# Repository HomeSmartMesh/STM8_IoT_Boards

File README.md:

# See these boards in action in the repo [IoT_Frameworks](https://github.com/wassfila/IoT_Frameworks)

# STM8_IoT_Boards
This repository provides PCBs based on the STM8 which is the cheapest microcontroller on the market (Low and production volumes) with the cheapest debug and development environment.

## IoT Node (RF but Connected to Power)
PCB design using the STM8S103F bread board with the nRF24L01+ module. Provides connectors for I²C, UART and One wire.
 - [STM8S fixed Node wiki page](http://technolab.ddns.net/display/SSN/STM8S+Fixed+Node)

## Smart IoT Node (Wireless and Cell Coin Powered)
This Board includes an STM8L151F3P6 (Low Power) the nRF24L01+, sensors modules : BMP280 (pressure, humidity, temperature), a MAX44009 (Ambient Light) and MRMS211H (Magnetic switches).
 - [STM8L Mobile Node wiki page](http://technolab.ddns.net/display/SSN/STM8L+Mobile+Node)

## IO_Expander
serial port commands issued in an ULN2804 general purpose up to 48V or 500mA per output
 - [Github Repository for nodejs websocket server with javascript gui](https://github.com/wassfila/smartio)
 - [IO Expander wiki page](http://technolab.ddns.net/display/SSN/Smart+IO+Expander)

## Servomotor Controller
This board uses the 16 bit x7 channels PWM (from different timers) used to generate pulses for servomotors.
 - [Available PS4 wireless on Raspberry Pi 3 application source codes](https://github.com/wassfila/joystick_servo)

# Links to Firmware Sources
 - [Hello World Examples](https://github.com/wassfila/STM8_IoT_HelloWorld)
 - [Complete Usecase Examples e.g. Sender + Receiver](https://github.com/wassfila/STM8_IoT_Base)

# More Info
The IoT node is an STM8 based low cost development platform.
It is an initiative for an open product = open hardware + open source project.
find all the details in this link :
http://www.homesmartmesh.com/mediawiki/index.php/IoT_Node

This board will be interfacing such peripherals :
 - Radio transceiver module
 - Weather sensors : temperature, humidity, air quality.
 - RGB Leds
 - Gyro / Accel
 - Ambient light and user gesture

The wiki above contains links to SW and HW, but here's a direct link to the Firmware open source project:
https://github.com/wassfila/STM8_IoT_HelloWorld
The Firmware contains drivers (in development) for the above mentionned peripherals.

This IoT Node is part of a bigger project that extand the collaboration to a complete IoT environment.
It includes  interfaces to existing products and server applications for merging everything together.
The "Home Smart Mesh" concept is described in the main wiki page
http://www.homesmartmesh.com/mediawiki/index.php/Main_Page

The Board is grouping two modules :
 - STM8 Dev Board based on the STM8S103F3
 - nRF24L01+ module based on the reference design
 - It also has a pullup resistor and 3 pins where to plug an DS18B20 temperature sensor

# License
- It is possible to use these designs for commercial purpose
- It is possible to modify the designs
- It is not necessary to mention the original author of these designs
- It is possible to add your own name or company on the design
- It is not possible to prevent anyone else from having the rights mentionned above

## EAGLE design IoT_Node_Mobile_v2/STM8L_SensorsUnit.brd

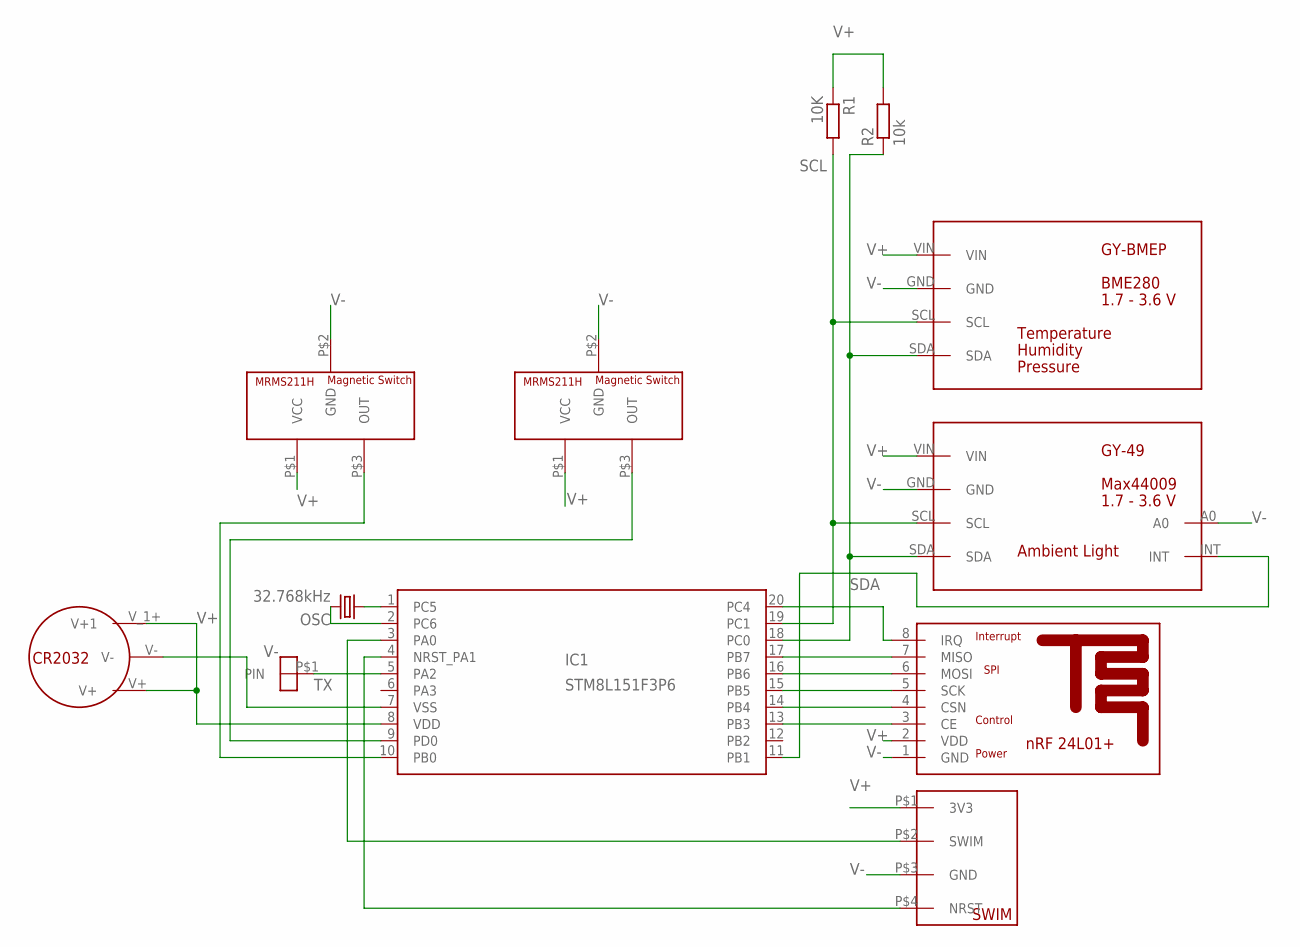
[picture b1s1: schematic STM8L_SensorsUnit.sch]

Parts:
IC1: STM8L151F3P6; STM8L151F3P
OSC: 32.768kHz; CRYSTAL-SMD-3.2X1.5MM
R1: 10K; M1206
R2: 10k; M1206
U$1: NRF24L01+REFDESIGNMINI; NRF24L01+REFDESIGN-MINI
U$2: GY-49G-49-SURF; GY-49-SURF
U$3: GY-BMEPGY-BMEP-NOHOLE; GY-BMEP-NOHOLE
U$4, U$6: MRMS211H-MAGNETIC-SWITCH; 3PIN-MM
U$5: CR2032-ISOLATED
U$7: SWIM
U$8: PINSIGNAL; PIN

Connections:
unnamed: IC1.16 (PB6), U$1.6 (MOSI)
unnamed: IC1.14 (PB4), U$1.4 (CSN)
unnamed: IC1.13 (PB3), U$1.3 (CE)
unnamed: IC1.10 (PB0), U$6.P$3 (OUT)
unnamed: IC1.9 (PD0), U$4.P$3 (OUT)
unnamed: IC1.20 (PC4), U$1.8 (IRQ)
unnamed: IC1.3 (PA0), U$7.P$2 (SWIM)
unnamed: IC1.4 (NRST_PA1), U$7.P$4 (NRST)
unnamed: IC1.1 (PC5), OSC.P$1 (1)
unnamed: IC1.11 (PB1), U$2.INT
unnamed: IC1.2 (PC6), OSC.P$2 (2)
unnamed: IC1.17 (PB7), U$1.7 (MISO)
unnamed: IC1.15 (PB5), U$1.5 (SCK)
SCL: IC1.19 (PC1), R1.2, U$2.SCL, U$3.SCL
SDA: IC1.18 (PC0), R2.1, U$2.SDA, U$3.SDA
TX: IC1.5 (PA2), U$8.P$1
V+: IC1.8 (VDD), R1.1, R2.2, U$1.2 (VDD), U$2.VIN, U$3.VIN, U$4.P$1 (VCC), U$5.V+, U$5.V_1+ (V+1), U$6.P$1 (VCC), U$7.P$1 (3V3)
V-: IC1.7 (VSS), U$1.1 (GND), U$2.A0, U$2.GND, U$3.GND, U$4.P$2 (GND), U$5.V-, U$6.P$2 (GND), U$7.P$3 (GND)

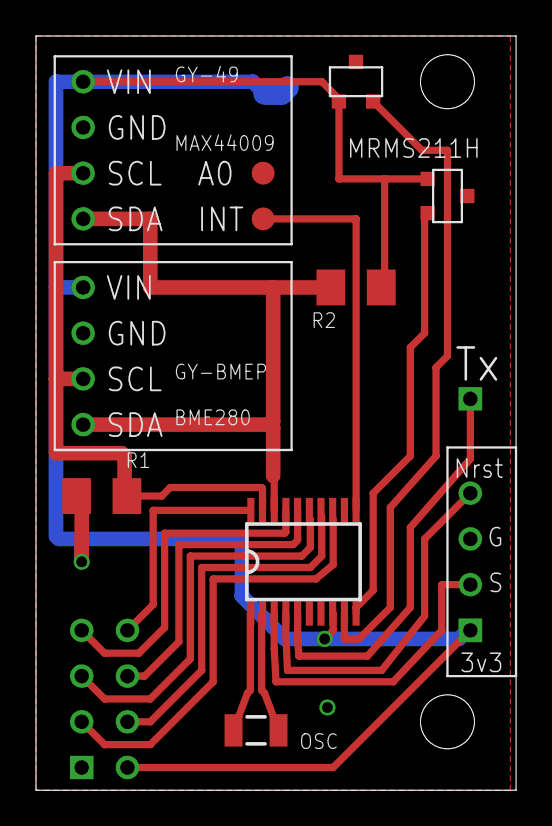
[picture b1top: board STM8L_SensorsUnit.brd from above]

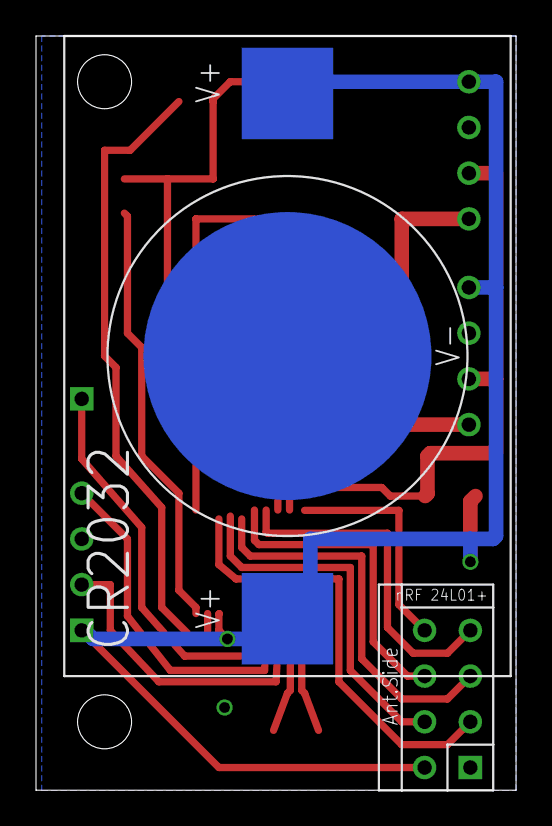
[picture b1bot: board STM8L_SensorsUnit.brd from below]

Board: 2 copper layers, 26.7 x 41.9 mm, 12 parts (2 on the bottom side), 18 nets.

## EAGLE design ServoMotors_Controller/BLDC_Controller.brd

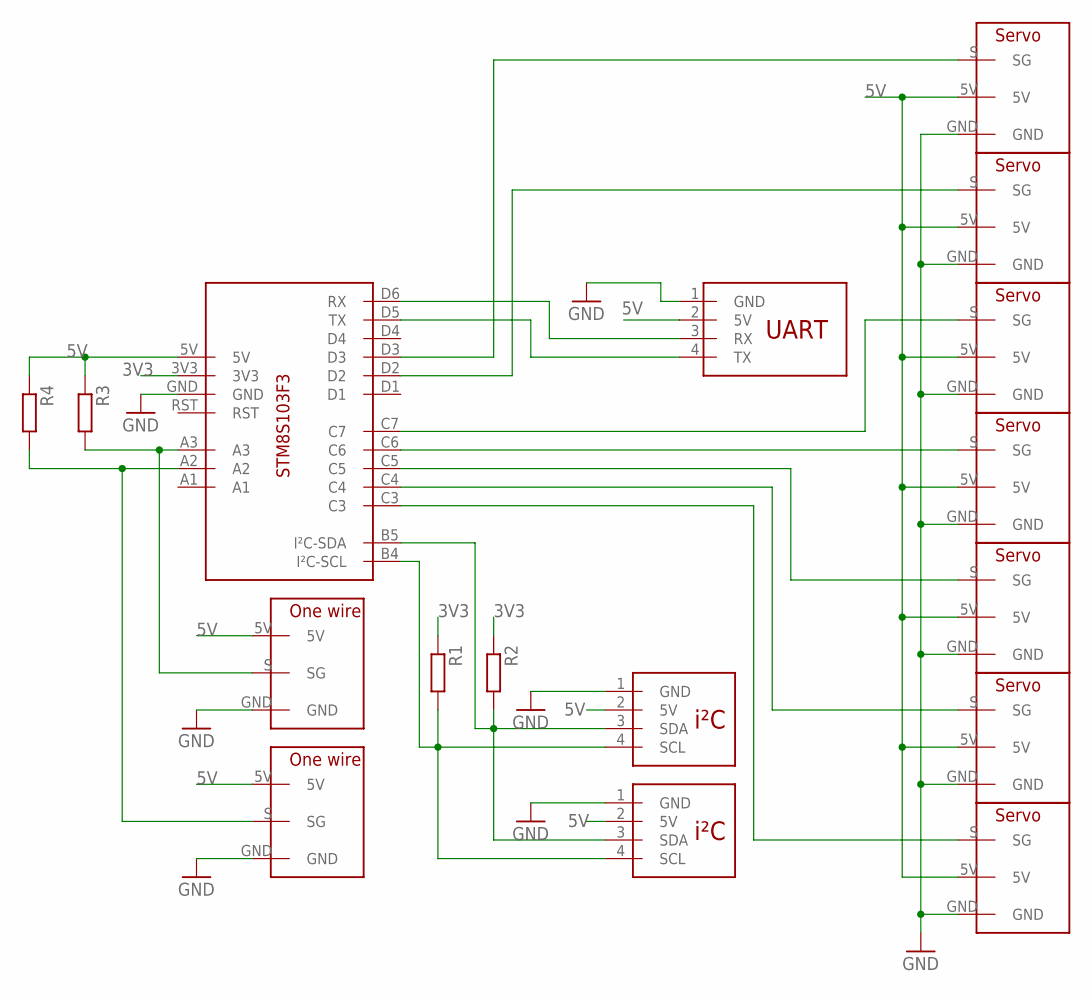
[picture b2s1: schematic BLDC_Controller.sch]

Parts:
R1, R2, R3, R4: 1k; R1206
U$1: STM8S103F3-DEVKITMINI; STM8S103F3-DEVKIT-MINI
U$2, U$8, U$9, U$10, U$11, U$12, U$13: SERVO
U$3: UARTMINI; UART-MINI
U$4, U$7: I2CMINI; I2C-MINI
U$5, U$6: ONE_WIRE

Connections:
3V3: R1.1, R2.1, U$1.3V3
5V: R3.1, R4.1, U$1.5V, U$2.5V, U$3.2 (5V), U$4.2 (5V), U$5.5V, U$6.5V, U$7.2 (5V), U$8.5V, U$9.5V, U$10.5V, U$11.5V, U$12.5V, U$13.5V
GND: U$1.GND, U$2.GND, U$3.1 (GND), U$4.1 (GND), U$5.GND, U$6.GND, U$7.1 (GND), U$8.GND, U$9.GND, U$10.GND, U$11.GND, U$12.GND, U$13.GND
unnamed: U$1.D5 (TX), U$3.4 (TX)
unnamed: U$1.C3, U$13.S (SG)
unnamed: U$1.C4, U$12.S (SG)
unnamed: U$1.C5, U$10.S (SG)
unnamed: U$1.C6, U$9.S (SG)
unnamed: U$1.C7, U$8.S (SG)
unnamed: R2.2, U$1.B5 (I²C-SDA), U$4.3 (SDA), U$7.3 (SDA)
unnamed: U$1.D2, U$2.S (SG)
unnamed: U$1.D6 (RX), U$3.3 (RX)
unnamed: R3.2, U$1.A3, U$6.S (SG)
unnamed: U$1.D3, U$11.S (SG)
unnamed: R4.2, U$1.A2, U$5.S (SG)
unnamed: R1.2, U$1.B4 (I²C-SCL), U$4.4 (SCL), U$7.4 (SCL)

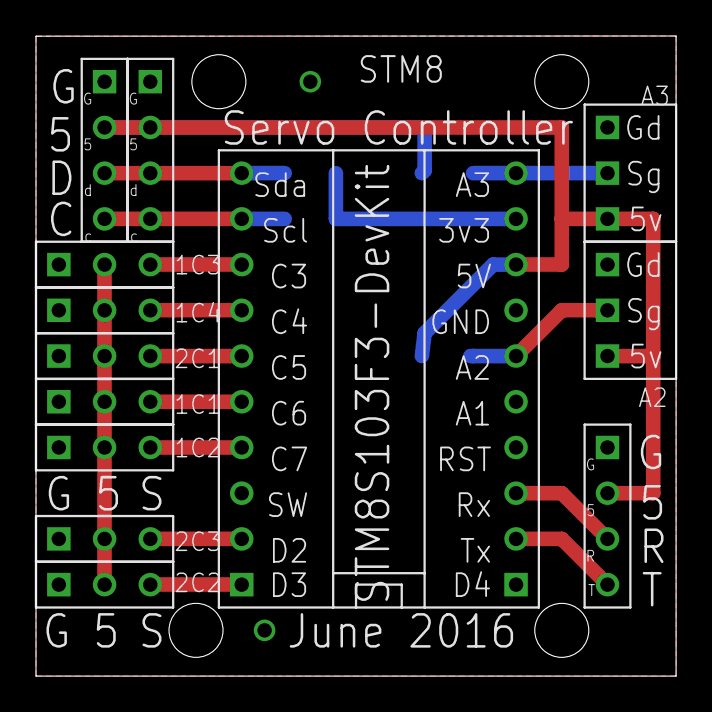
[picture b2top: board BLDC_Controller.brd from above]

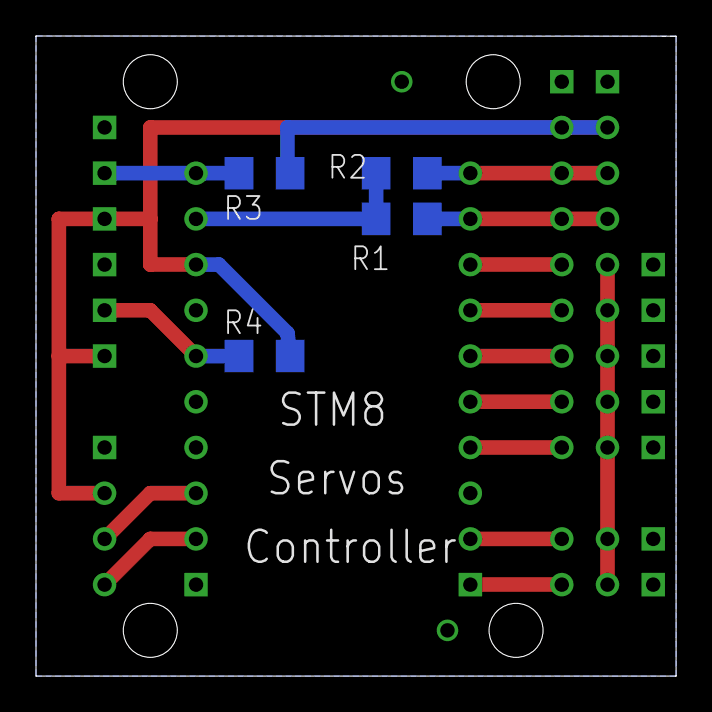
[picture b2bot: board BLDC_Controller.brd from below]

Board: 2 copper layers, 35.6 x 35.6 mm, 17 parts (4 on the bottom side), 16 nets.

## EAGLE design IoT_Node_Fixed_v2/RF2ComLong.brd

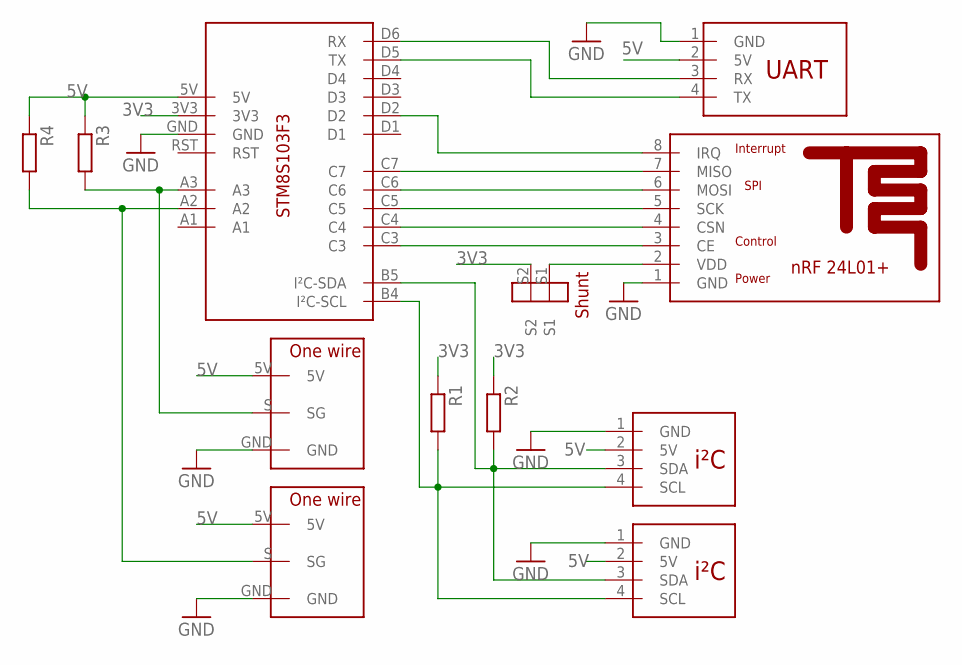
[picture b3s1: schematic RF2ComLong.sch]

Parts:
R1, R2, R3, R4: 1k; R1206
U$1: STM8S103F3-DEVKITMINI; STM8S103F3-DEVKIT-MINI
U$2: NRF24L01+REFDESIGNMINI; NRF24L01+REFDESIGN-MINI
U$3: UARTMINI; UART-MINI
U$4, U$7: I2CMINI; I2C-MINI
U$5, U$6: ONE_WIRE
U$8: SMD_SHUNT

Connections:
3V3: R1.1, R2.1, U$1.3V3, U$8.S2
5V: R3.1, R4.1, U$1.5V, U$3.2 (5V), U$4.2 (5V), U$5.5V, U$6.5V, U$7.2 (5V)
GND: U$1.GND, U$2.1 (GND), U$3.1 (GND), U$4.1 (GND), U$5.GND, U$6.GND, U$7.1 (GND)
unnamed: U$1.D5 (TX), U$3.4 (TX)
unnamed: U$1.C3, U$2.3 (CE)
unnamed: U$1.C4, U$2.4 (CSN)
unnamed: U$1.C5, U$2.5 (SCK)
unnamed: U$1.C6, U$2.6 (MOSI)
unnamed: U$1.C7, U$2.7 (MISO)
unnamed: R2.2, U$1.B5 (I²C-SDA), U$4.3 (SDA), U$7.3 (SDA)
unnamed: U$1.D2, U$2.8 (IRQ)
unnamed: U$1.D6 (RX), U$3.3 (RX)
unnamed: R3.2, U$1.A3, U$6.S (SG)
unnamed: R4.2, U$1.A2, U$5.S (SG)
unnamed: R1.2, U$1.B4 (I²C-SCL), U$4.4 (SCL), U$7.4 (SCL)
unnamed: U$2.2 (VDD), U$8.S1

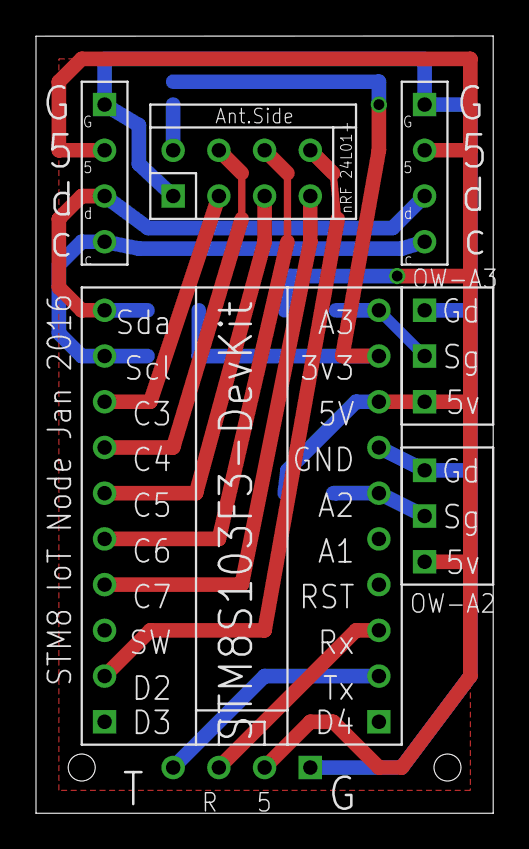
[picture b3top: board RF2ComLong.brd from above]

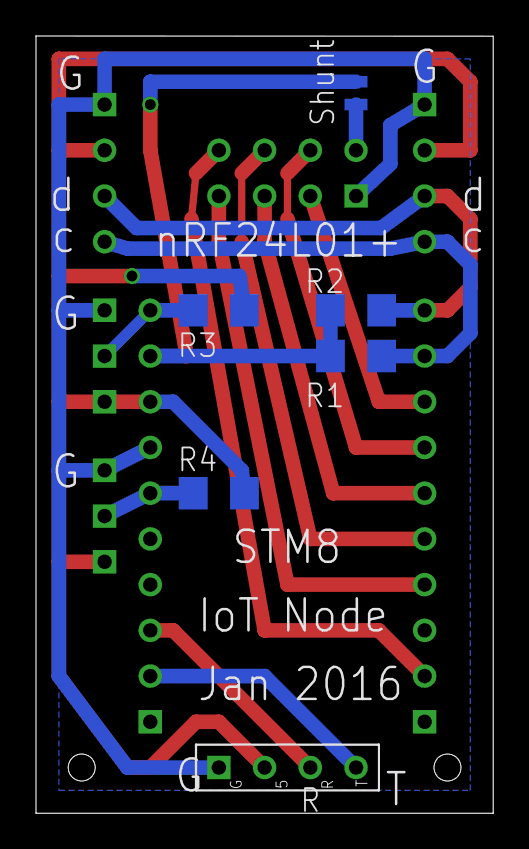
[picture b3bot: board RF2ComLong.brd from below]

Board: 2 copper layers, 25.4 x 43.2 mm, 12 parts (6 on the bottom side), 16 nets.

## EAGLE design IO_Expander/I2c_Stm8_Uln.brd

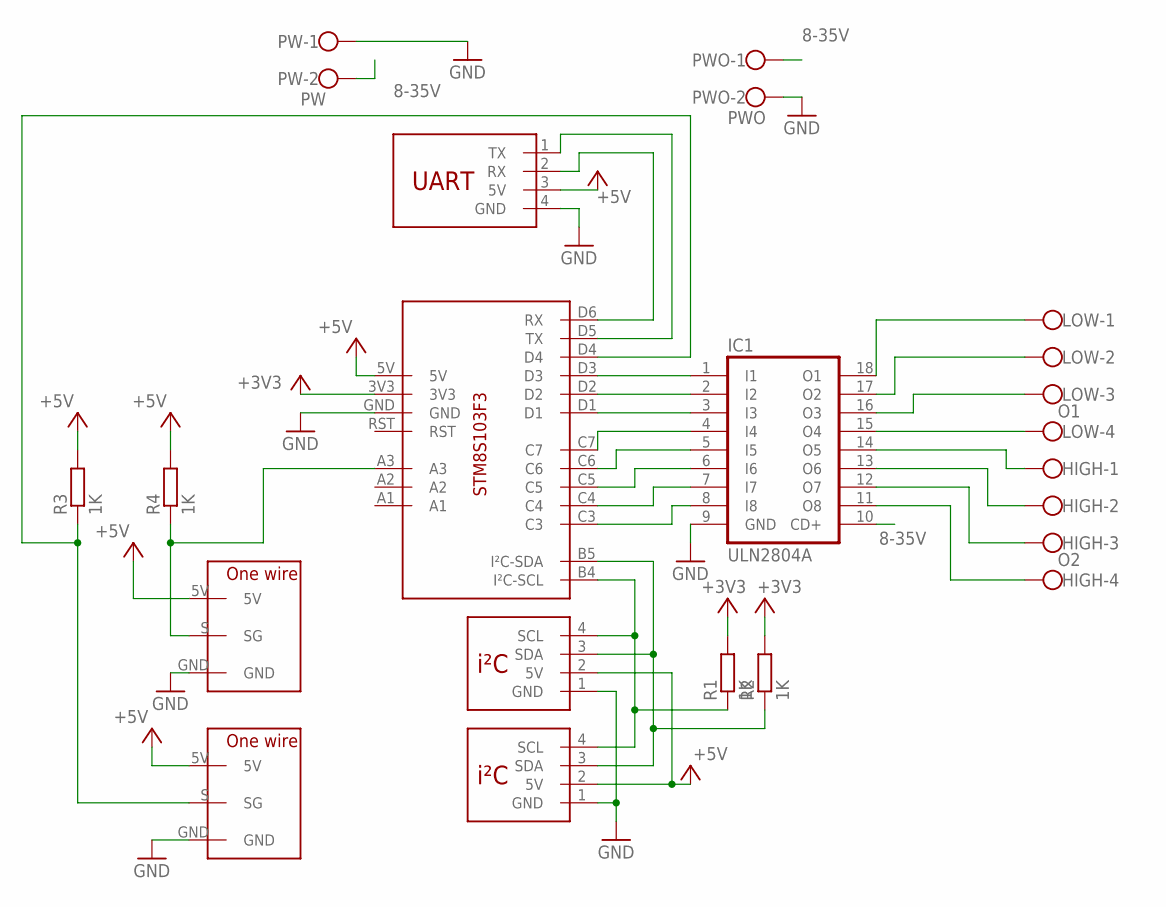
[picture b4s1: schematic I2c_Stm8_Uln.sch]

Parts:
HIGH: O2; W237-4
I2C, I2C_SHARE: I2C
IC1: ULN2804A; DIL18
LOW: O1; W237-4
PW: PW; W237-102
PWO: PWO; W237-102
R1, R2, R3, R4: 1K; R1206
U$1: STM8S103F3-DEVKIT
U$2, U$4: ONE_WIRE
U$3: UARTBIG; UART

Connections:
8-35V: IC1.10 (CD+), PW.2, PWO.1
+3V3: R1.2, R2.2, U$1.3V3
+5V: I2C.2 (5V), I2C_SHARE.2 (5V), R3.2, R4.2, U$1.5V, U$2.5V, U$3.3 (5V), U$4.5V
GND: I2C.1 (GND), I2C_SHARE.1 (GND), IC1.9 (GND), PW.1, PWO.2, U$1.GND, U$2.GND, U$3.4 (GND), U$4.GND
unnamed: U$1.D6 (RX), U$3.2 (RX)
unnamed: I2C.4 (SCL), I2C_SHARE.4 (SCL), R1.1, U$1.B4 (I²C-SCL)
unnamed: I2C.3 (SDA), I2C_SHARE.3 (SDA), R2.1, U$1.B5 (I²C-SDA)
unnamed: U$1.D5 (TX), U$3.1 (TX)
unnamed: IC1.1 (I1), U$1.D3
unnamed: IC1.2 (I2), U$1.D2
unnamed: IC1.3 (I3), U$1.D1
unnamed: IC1.4 (I4), U$1.C7
unnamed: IC1.5 (I5), U$1.C6
unnamed: IC1.6 (I6), U$1.C5
unnamed: IC1.7 (I7), U$1.C4
unnamed: IC1.8 (I8), U$1.C3
unnamed: IC1.18 (O1), LOW.1
unnamed: IC1.17 (O2), LOW.2
unnamed: IC1.16 (O3), LOW.3
unnamed: IC1.15 (O4), LOW.4
unnamed: HIGH.1, IC1.14 (O5)
unnamed: HIGH.2, IC1.13 (O6)
unnamed: HIGH.3, IC1.12 (O7)
unnamed: HIGH.4, IC1.11 (O8)
unnamed: R3.1, U$1.D4, U$4.S (SG)
unnamed: R4.1, U$1.A3, U$2.S (SG)

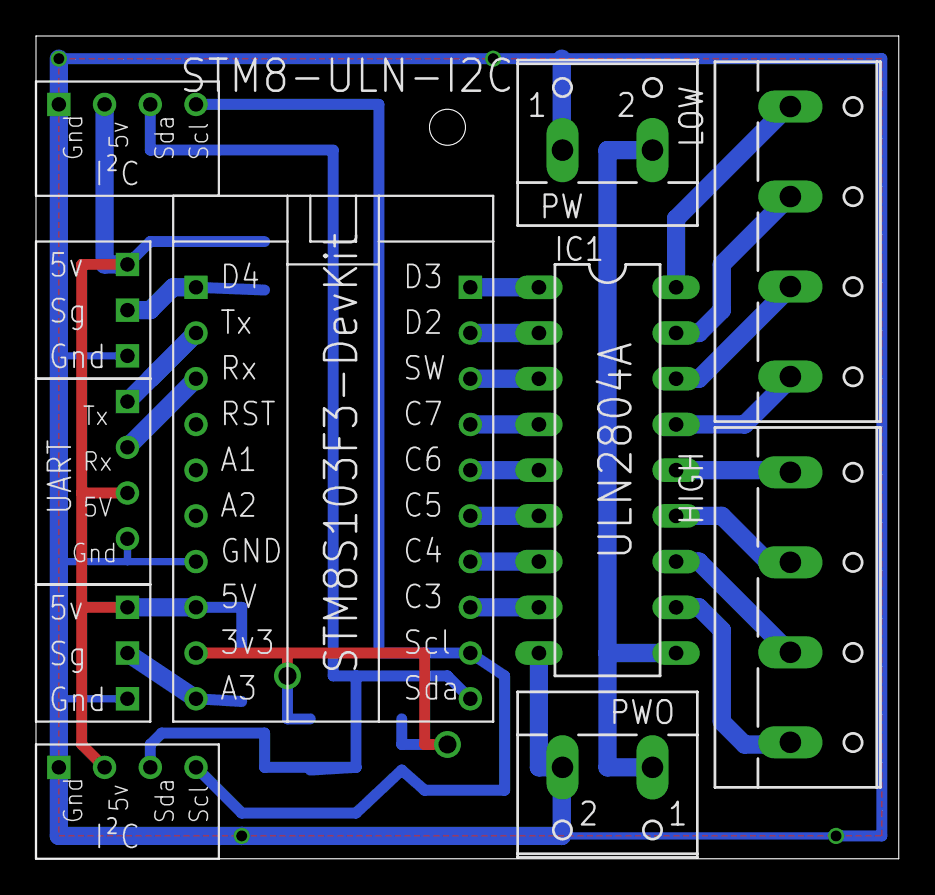
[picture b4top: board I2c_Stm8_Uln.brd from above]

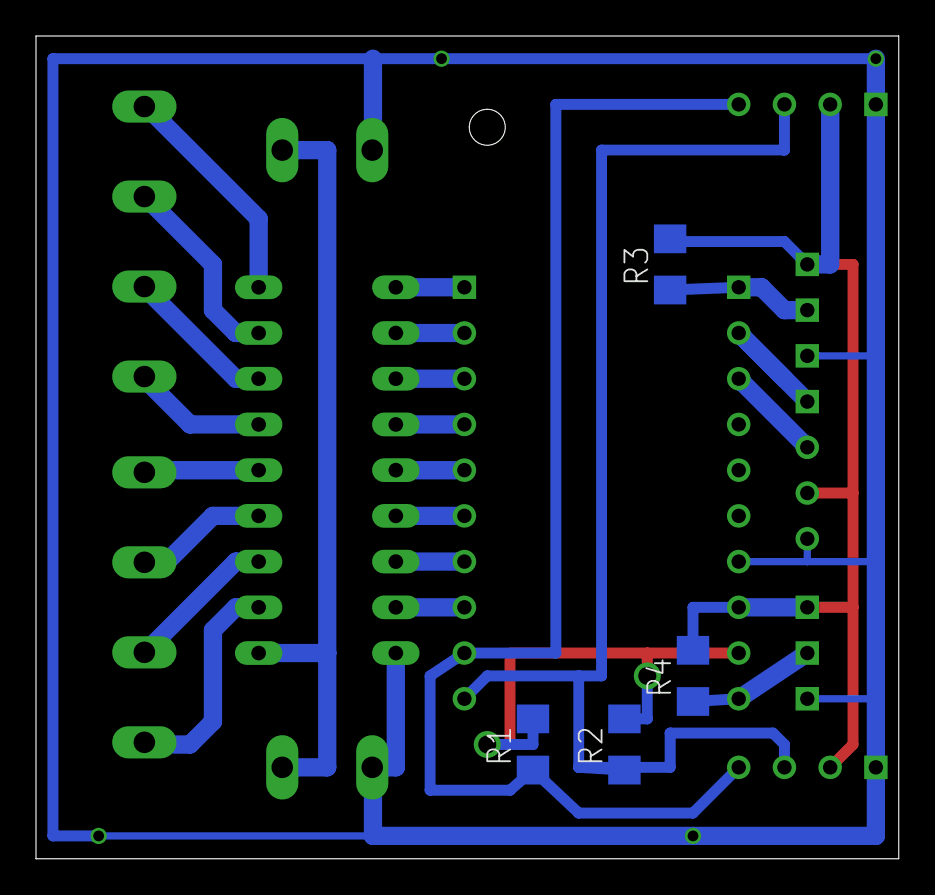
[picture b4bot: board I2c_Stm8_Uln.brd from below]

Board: 2 copper layers, 47.9 x 45.7 mm, 15 parts (4 on the bottom side), 26 nets.

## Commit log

2015-12-10 :space_invader: Added .gitattributes & .gitignore files
2015-12-10 First version of the IoT Node
    This is the first version shared under the package
    eagle_SmartUnit_2015-12-06.zip
2015-12-10 Added link to the Forum
2015-12-10 Liberal license agreement added
2016-09-25 Commited all current Board versions (IoT_Node Fixed v2, Mobile v2, IO Expander and Servo Motors Controller)
2016-09-26 added photos of the Boards
2016-09-26 Added Board photos on read me

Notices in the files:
parts and their libraries:
SparkFun-FreqCtrl: Licensing: Creative Commons ShareAlike 4.0 International - https://creativecommons.org/licenses/by-sa/4.0
